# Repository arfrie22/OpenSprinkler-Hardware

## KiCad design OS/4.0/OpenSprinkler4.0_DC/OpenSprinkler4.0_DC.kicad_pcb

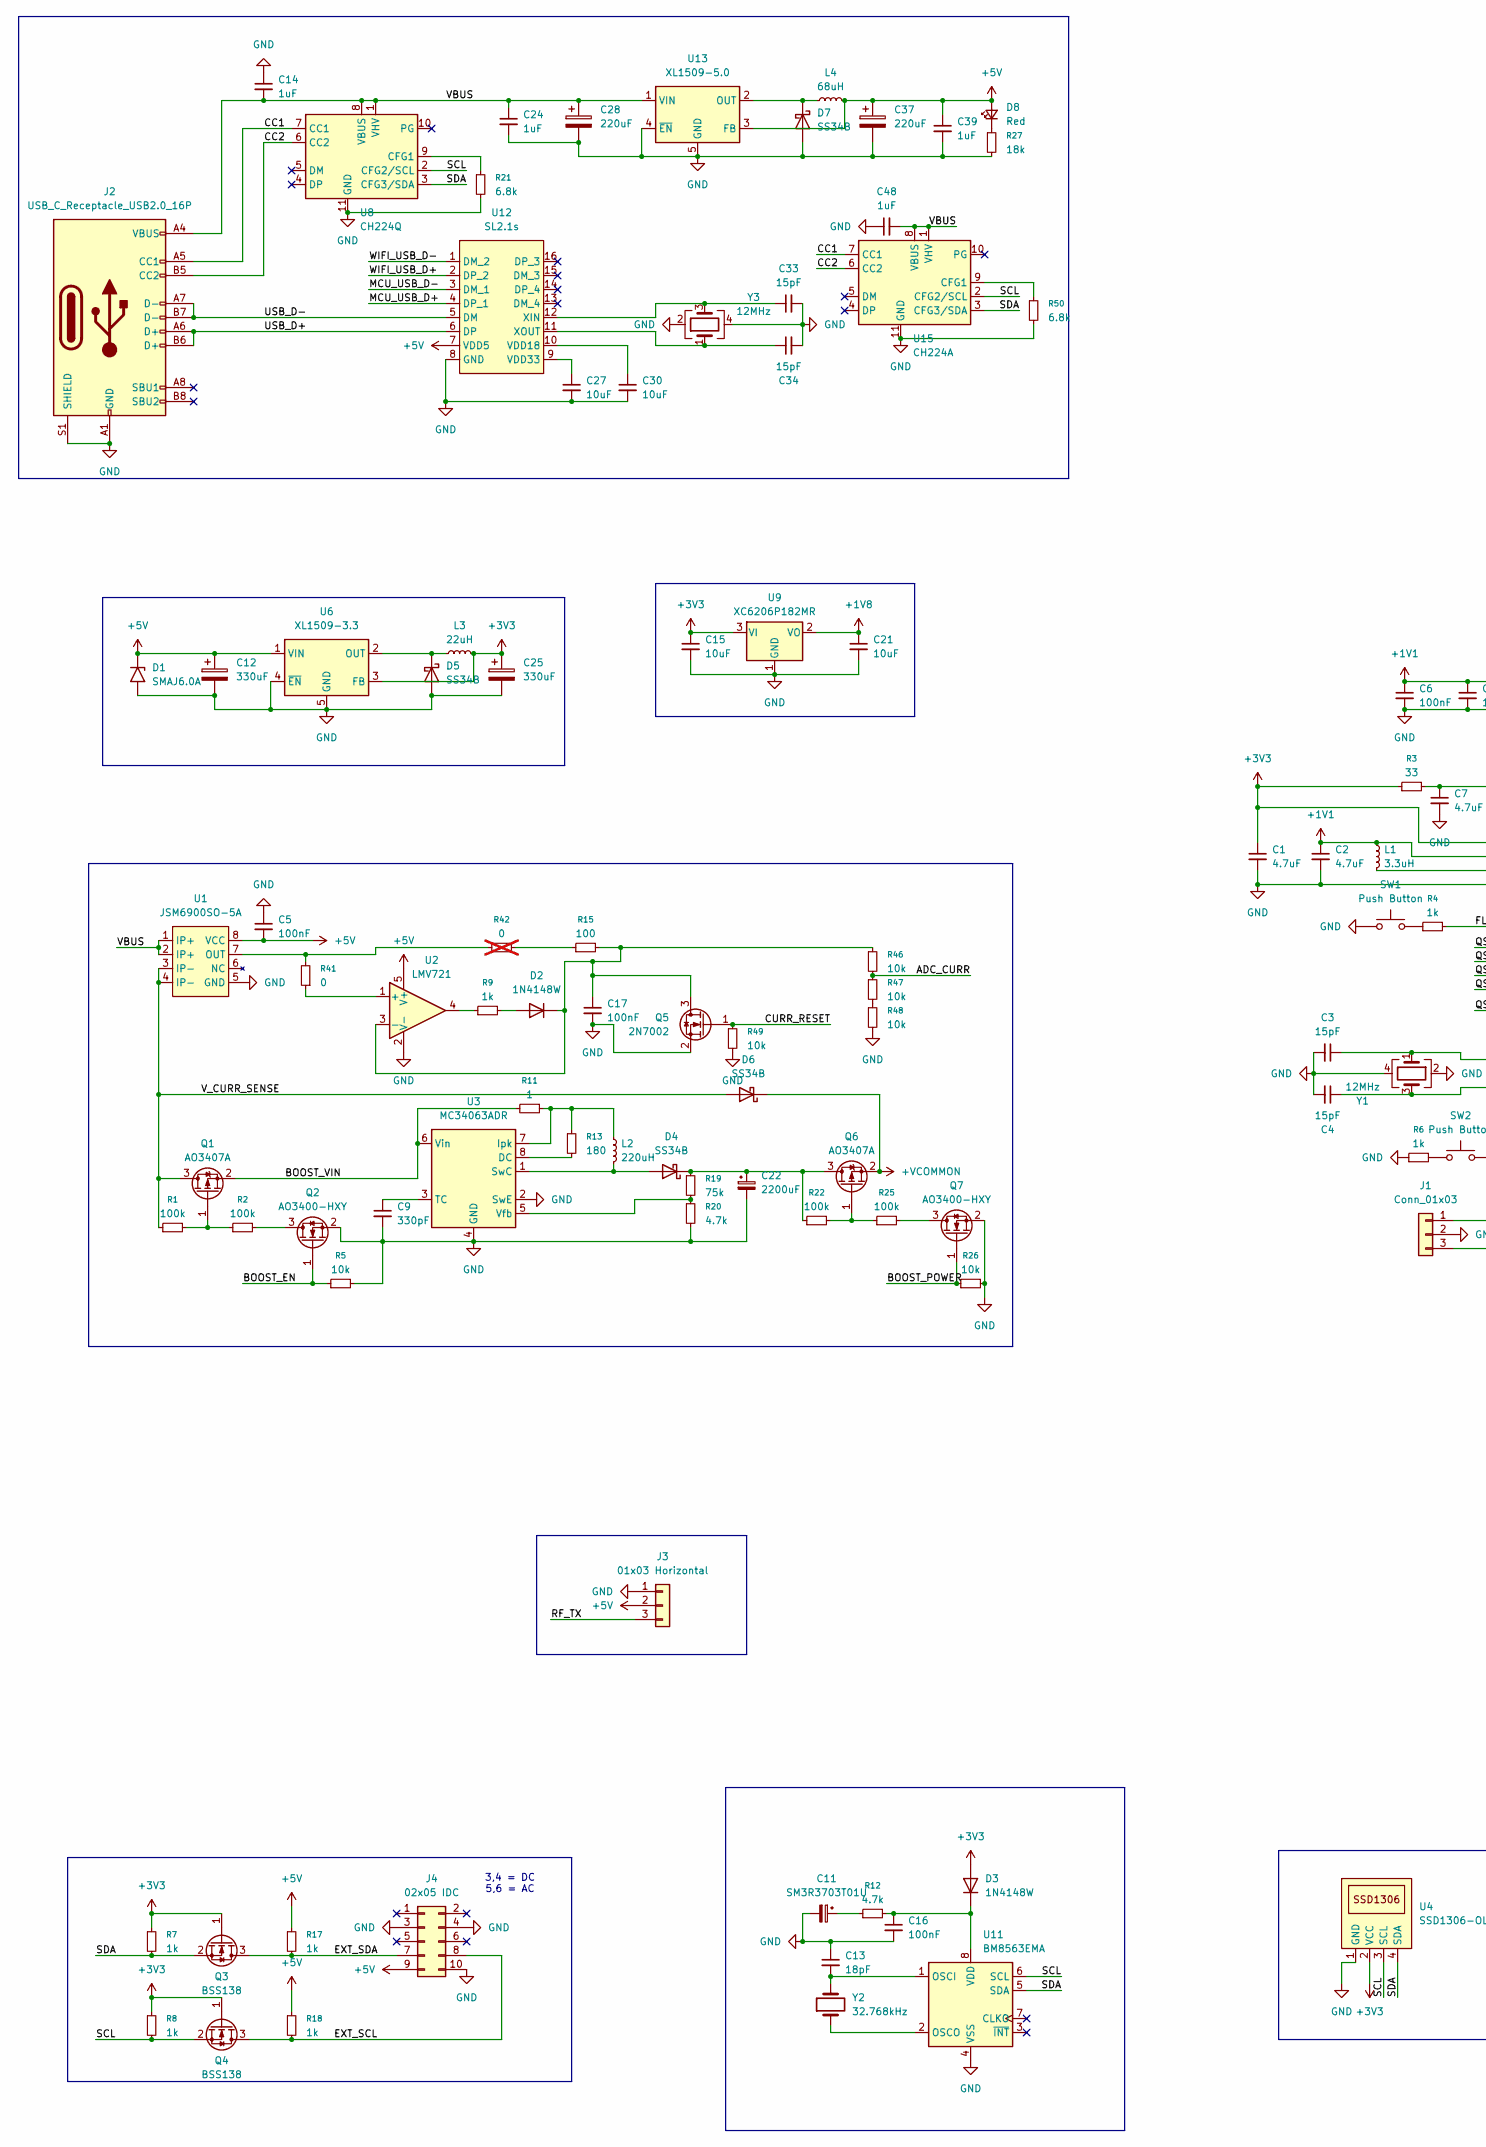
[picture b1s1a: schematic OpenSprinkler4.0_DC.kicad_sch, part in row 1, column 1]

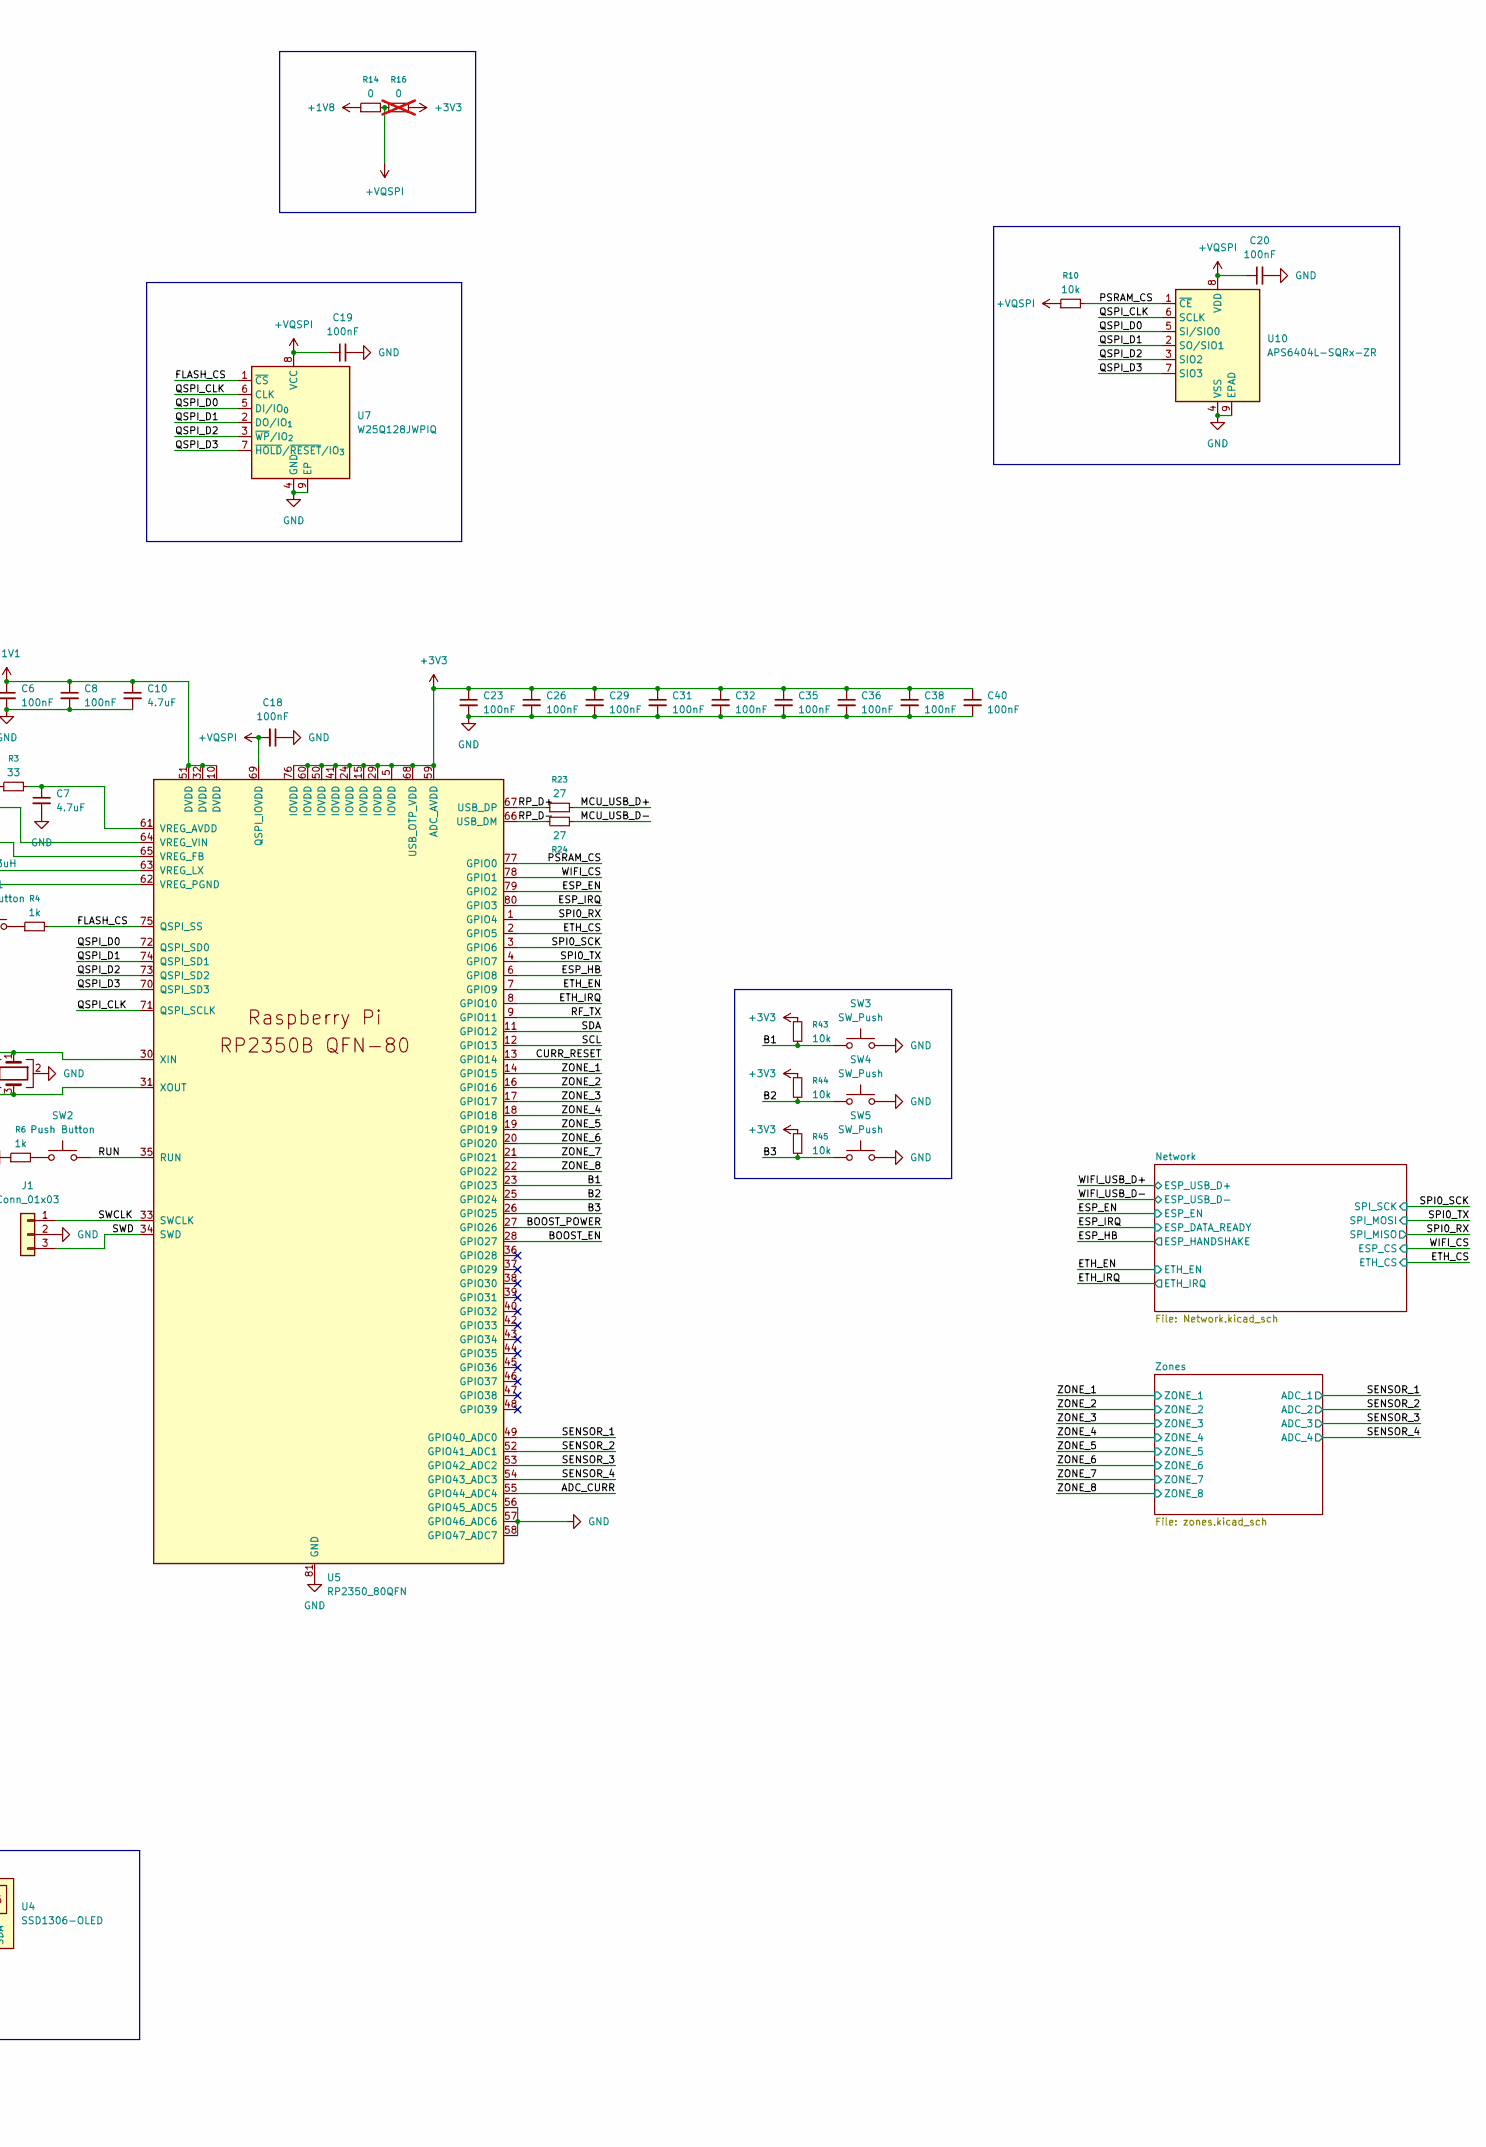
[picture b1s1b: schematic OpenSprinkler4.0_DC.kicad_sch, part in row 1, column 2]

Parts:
C1, C2, C7, C10: 4.7uF; C_0402_1005Metric; LCSC C23733
C3, C4, C33, C34: 15pF; C_0402_1005Metric; LCSC C1548
C5, C6, C8, C16, C17, C18, C19, C20, C23, C26, C29, C31, C32, C35, C36, C38, C40: 100nF; C_0402_1005Metric; LCSC C307331
C9: 330pF; C_0402_1005Metric; LCSC C13533
C11: SM3R3703T01U; SM3R3703T01
C12, C25: 330uF; CP_Radial_D8.0mm_P3.50mm; LCSC C43839
C13: 18pF; C_0402_1005Metric; LCSC C1549
C14, C24, C39, C48: 1uF; C_0603_1608Metric; LCSC C15849
C15, C21, C27, C30: 10uF; C_0603_1608Metric; LCSC C19702
C22: 2200uF; CP_Radial_L20.0mm_D13.0mm_P5.00mm_Horizontal; LCSC C44598
C28, C37: 220uF; CP_Radial_D6.3mm_P2.50mm; LCSC C12450
D1: SMAJ6.0A; D_SMA; LCSC C19077525
D2, D3: 1N4148W; D_SOD-123; LCSC C7420318
D4, D5, D6, D7: SS34B; D_SMB; LCSC C7420366
D8: Red; LED_0603_1608Metric; LCSC C2286
J1: Conn_01x03; JST_XH_B3B-XH-A_1x03_P2.50mm_Vertical; LCSC C144394
J2: USB_C_Receptacle_USB2.0_16P; USB_C_Receptacle_HRO_TYPE-C-31-M-12; LCSC C2927038
J3: 01x03 Horizontal; PinSocket_1x03_P2.54mm_Horizontal; LCSC C2935993
J4: 02x05 IDC; IDC-Header_2x05_P2.54mm_Horizontal; LCSC C9140
L1: 3.3uH; L_Murata_DFE201610P; LCSC C42411119
L2: 220uH; L_Changjiang_FNR8040S; LCSC C168148
L3: 22uH; L_Changjiang_FNR6045S; LCSC C168080
L4: 68uH; L_Changjiang_FNR6045S; LCSC C168091
Q1, Q6: AO3407A; SOT-23; LCSC C3033400
Q2, Q7: AO3400-HXY; SOT-23; LCSC C4748804
Q3, Q4: BSS138; SOT-23; LCSC C7420339
Q5: 2N7002; SOT-23; LCSC C8545
R1, R2, R22, R25: 100k; R_0402_1005Metric; LCSC C25741
R3: 33; R_0402_1005Metric; LCSC C25105
R4, R6, R7, R8, R9, R17, R18: 1k; R_0402_1005Metric; LCSC C11702
R5, R10, R26, R43, R44, R45, R46, R47, R48, R49: 10k; R_0402_1005Metric; LCSC C25744
R11: 1; R_0603_1608Metric; LCSC C22936
R12, R20: 4.7k; R_0402_1005Metric; LCSC C25900
R13: 180; R_0603_1608Metric; LCSC C22828
R14, R41: 0; R_0402_1005Metric; LCSC C17168
R15: 100; R_0402_1005Metric; LCSC C25076
R16, R42: 0; R_0402_1005Metric; LCSC C17168; not fitted
R19: 75k; R_0402_1005Metric; LCSC C25798
R21, R50: 6.8k; R_0402_1005Metric; LCSC C25917
R23, R24: 27; R_0402_1005Metric; LCSC C25100
R27: 18k; R_0402_1005Metric; LCSC C25762
SW1, SW2: Push Button; SW_SPST_SKQG_WithoutStem; LCSC C318884
SW3, SW4, SW5: SW_Push; SW_Tactile_SPST_Angled_PTS645Vx83-2LFS; LCSC C493019
U1: JSM6900SO-5A; SSOP-8_3.9x5.05mm_P1.27mm; LCSC C7496525
U2: LMV721; SOT-23-5; LCSC C20613263
U3: MC34063ADR; SOP-8_3.76x4.96mm_P1.27mm; LCSC C3014308
U4: SSD1306-OLED; JMD0.96D-1
U5: RP2350_80QFN; QFN-80-1EP_10x10mm_P0.4mm_EP3.4x3.4mm; LCSC C42415655
U6: XL1509-3.3; SOIC-8_3.9x4.9mm_P1.27mm; LCSC C2681226
U7: W25Q128JWPIQ; WSON-8-1EP_6x5mm_P1.27mm_EP3.4x4.3mm; LCSC C2689660
U8: CH224Q; Texas_DLH0010A_WSON-10-1EP_2.2x2mm_P0.4mm_EP0.9x1.5mm; LCSC C46061833
U9: XC6206P182MR; SOT-23-3; LCSC C347373
U10: APS6404L-SQRx-ZR; Winbond_USON-8-1EP_3x2mm_P0.5mm_EP0.2x1.6mm; LCSC C43758152
U11: BM8563EMA; SOIC-8_3.9x4.9mm_P1.27mm; LCSC C269878
U12: SL2.1s; SL2.1S; LCSC C2684433
U13: XL1509-5.0; SOIC-8_3.9x4.9mm_P1.27mm; LCSC C2902368
U15: CH224A; SSOP-10-1EP_3.9x4.9mm_P1mm_EP2.1x3.3mm; LCSC C42459160
Y1, Y3: 12MHz; Crystal_SMD_2520-4Pin_2.5x2.0mm; LCSC C7294610
Y2: 32.768kHz; Crystal_SMD_3215-2Pin_3.2x1.5mm; LCSC C32346

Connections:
+1V1: C2.1, C6.1, C8.1, C10.1, L1.1, U5.10 (DVDD), U5.32 (DVDD), U5.51 (DVDD), U5.65 (VREG_FB)
+1V8: C21.1, R14.1, U9.2 (VO)
+3V3: C1.1, C15.1, C23.1, C25.1, C26.1, C29.1, C31.1, C32.1, C35.1, C36.1, C38.1, C40.1, D3.2 (A), L3.2, Q3.1 (G), Q4.1 (G), R3.1, R7.1, R8.1, R16.2, R43.1, R44.1, R45.1, U4.2 (VCC), U5.5 (IOVDD), U5.15 (IOVDD), U5.24 (IOVDD), U5.29 (IOVDD), U5.41 (IOVDD), U5.50 (IOVDD), U5.59 (ADC_AVDD), U5.60 (IOVDD), U5.64 (VREG_VIN), U5.68 (USB_OTP_VDD), U5.76 (IOVDD), U6.3 (FB), U9.3 (VI); also elsewhere on the board
+5V: C5.2, C12.1, C37.1, C39.1, D1.1 (A1), D8.2 (A), J3.2, J4.9, L4.2, R17.1, R18.1, U1.8 (VCC), U2.5 (V+), U6.1 (VIN), U12.7 (VDD5), U13.3 (FB); also elsewhere on the board
+VQSPI: C18.2, C19.1, C20.1, R10.1, R14.2, R16.1, U5.69 (QSPI_IOVDD), U7.8 (VCC), U10.8 (VDD)
/ADC_CURR: R46.2, R47.1, U5.55 (GPIO44_ADC4)
/B1: R43.2, SW3.1, U5.23 (GPIO23)
/B2: R44.2, SW4.1, U5.25 (GPIO24)
/B3: R45.2, SW5.1, U5.26 (GPIO25)
/BOOST_EN: Q2.1 (G), R5.1, U5.28 (GPIO27)
/BOOST_POWER: Q7.1 (G), R26.1, U5.27 (GPIO26)
/BOOST_VIN: Q1.2 (S), R11.2, U3.6 (Vin)
/CC1: J2.A5 (CC1), U8.7 (CC1), U15.7 (CC1)
/CC2: J2.B5 (CC2), U8.6 (CC2), U15.6 (CC2)
/CURR_RESET: Q5.1 (G), R49.1, U5.13 (GPIO14)
/ESP_EN: U5.79 (GPIO2); also elsewhere on the board
/ESP_HB: U5.6 (GPIO8); also elsewhere on the board
/ESP_IRQ: U5.80 (GPIO3); also elsewhere on the board
/ETH_CS: U5.2 (GPIO5); also elsewhere on the board
/ETH_EN: U5.7 (GPIO9); also elsewhere on the board
/ETH_IRQ: U5.8 (GPIO10); also elsewhere on the board
/EXT_SCL: J4.8, Q4.3 (D), R18.2
/EXT_SDA: J4.7, Q3.3 (D), R17.2
/FLASH_CS: R4.2, U5.75 (QSPI_SS), U7.1 (~CS)
/MCU_USB_D+: R23.2, U12.4 (DP_1)
/MCU_USB_D-: R24.2, U12.3 (DM_1)
/PSRAM_CS: R10.2, U5.77 (GPIO0), U10.1 (~CE)
/QSPI_CLK: U5.71 (QSPI_SCLK), U7.6 (CLK), U10.6 (SCLK)
/QSPI_D0: U5.72 (QSPI_SD0), U7.5 (DI/IO_{0}), U10.5 (SI/SIO0)
/QSPI_D1: U5.74 (QSPI_SD1), U7.2 (DO/IO_{1}), U10.2 (SO/SIO1)
/QSPI_D2: U5.73 (QSPI_SD2), U7.3 (~WP/IO_{2}), U10.3 (SIO2)
/QSPI_D3: U5.70 (QSPI_SD3), U7.7 (~HOLD/~RESET/IO_{3}), U10.7 (SIO3)
/RF_TX: J3.3, U5.9 (GPIO11)
/RP_D+: R23.1, U5.67 (USB_DP)
/RP_D-: R24.1, U5.66 (USB_DM)
/RUN: SW2.2, U5.35 (RUN)
/SCL: Q4.2 (S), R8.2, U4.3 (SCL), U5.12 (GPIO13), U8.2 (CFG2/SCL), U11.6 (SCL), U15.2 (CFG2/SCL)
/SDA: Q3.2 (S), R7.2, U4.4 (SDA), U5.11 (GPIO12), U8.3 (CFG3/SDA), U11.5 (SDA), U15.3 (CFG3/SDA)
/SENSOR_1: U5.49 (GPIO40_ADC0); also elsewhere on the board
/SENSOR_2: U5.52 (GPIO41_ADC1); also elsewhere on the board
/SENSOR_3: U5.53 (GPIO42_ADC2); also elsewhere on the board
/SENSOR_4: U5.54 (GPIO43_ADC3); also elsewhere on the board
/SPI0_RX: U5.1 (GPIO4); also elsewhere on the board
/SPI0_SCK: U5.3 (GPIO6); also elsewhere on the board
/SPI0_TX: U5.4 (GPIO7); also elsewhere on the board
/SWCLK: J1.1, U5.33 (SWCLK)
/SWD: J1.3, U5.34 (SWD)
/USB_D+: J2.A6 (D+), J2.B6 (D+), U12.6 (DP)
/USB_D-: J2.A7 (D-), J2.B7 (D-), U12.5 (DM)
/VBUS: C14.2, C24.1, C28.1, C48.2, J2.A4 (VBUS), J2.A9 (VBUS), J2.B4 (VBUS), J2.B9 (VBUS), U1.1 (IP+), U1.2 (IP+), U8.1 (VHV), U8.8 (VBUS), U13.1 (VIN), U15.1 (VHV), U15.8 (VBUS)
/V_CURR_SENSE: D6.2 (A), Q1.3 (D), R1.1, U1.3 (IP-), U1.4 (IP-)
/WIFI_CS: U5.78 (GPIO1); also elsewhere on the board
/WIFI_USB_D+: U12.2 (DP_2); also elsewhere on the board
/WIFI_USB_D-: U12.1 (DM_2); also elsewhere on the board
/ZONE_1: U5.14 (GPIO15); also elsewhere on the board
/ZONE_2: U5.16 (GPIO16); also elsewhere on the board
/ZONE_3: U5.17 (GPIO17); also elsewhere on the board
/ZONE_4: U5.18 (GPIO18); also elsewhere on the board
/ZONE_5: U5.19 (GPIO19); also elsewhere on the board
/ZONE_6: U5.20 (GPIO20); also elsewhere on the board
/ZONE_7: U5.21 (GPIO21); also elsewhere on the board
/ZONE_8: U5.22 (GPIO22); also elsewhere on the board
unnamed: C11.1, R12.1
unnamed: D2.2 (A), R9.2
unnamed: C17.1, D2.1 (K), Q5.3 (D), R15.2, R46.1, U2.3 (-)
unnamed: C16.1, D3.1 (K), R12.2, U11.8 (VDD)
unnamed: D4.2 (A), L2.2, U3.1 (SwC)
unnamed: C22.1, D4.1 (K), Q6.3 (D), R19.1, R22.1
unnamed: D5.1 (K), L3.1, U6.2 (OUT)
unnamed: D7.1 (K), L4.1, U13.2 (OUT)
unnamed: D8.1 (K), R27.1
unnamed: Q1.1 (G), R1.2, R2.1
unnamed: Q2.3 (D), R2.2
unnamed: Q6.1 (G), R22.2, R25.1
unnamed: Q7.3 (D), R25.2
unnamed: R4.1, SW1.2
unnamed: R6.2, SW2.1
unnamed: R9.1, U2.4
unnamed: R15.1, R42.2
unnamed: R47.2, R48.1
unnamed: R41.2, R42.1, U1.7 (OUT)
unnamed: R41.1, U2.1 (+)
unnamed: R13.2, U3.8 (DC)
unnamed: L2.1, R11.1, R13.1, U3.7 (Ipk)
unnamed: C9.1, U3.3 (TC)
unnamed: R19.2, R20.1, U3.5 (Vfb)
unnamed: C7.1, R3.2, U5.61 (VREG_AVDD)
unnamed: L1.2, U5.63 (VREG_LX)
unnamed: C3.1, U5.30 (XIN), Y1.1
unnamed: C4.1, U5.31 (XOUT), Y1.3
unnamed: R21.1, U8.9 (CFG1)
unnamed: C13.2, U11.1 (OSCI), Y2.2
unnamed: U11.2 (OSCO), Y2.1
unnamed: C30.1, U12.10 (VDD18)
unnamed: C27.1, U12.9 (VDD33)
unnamed: C33.1, U12.12 (XIN), Y3.3
unnamed: C34.1, U12.11 (XOUT), Y3.1
unnamed: R50.1, U15.9 (CFG1)

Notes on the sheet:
3,4 = DC 5,6 = AC

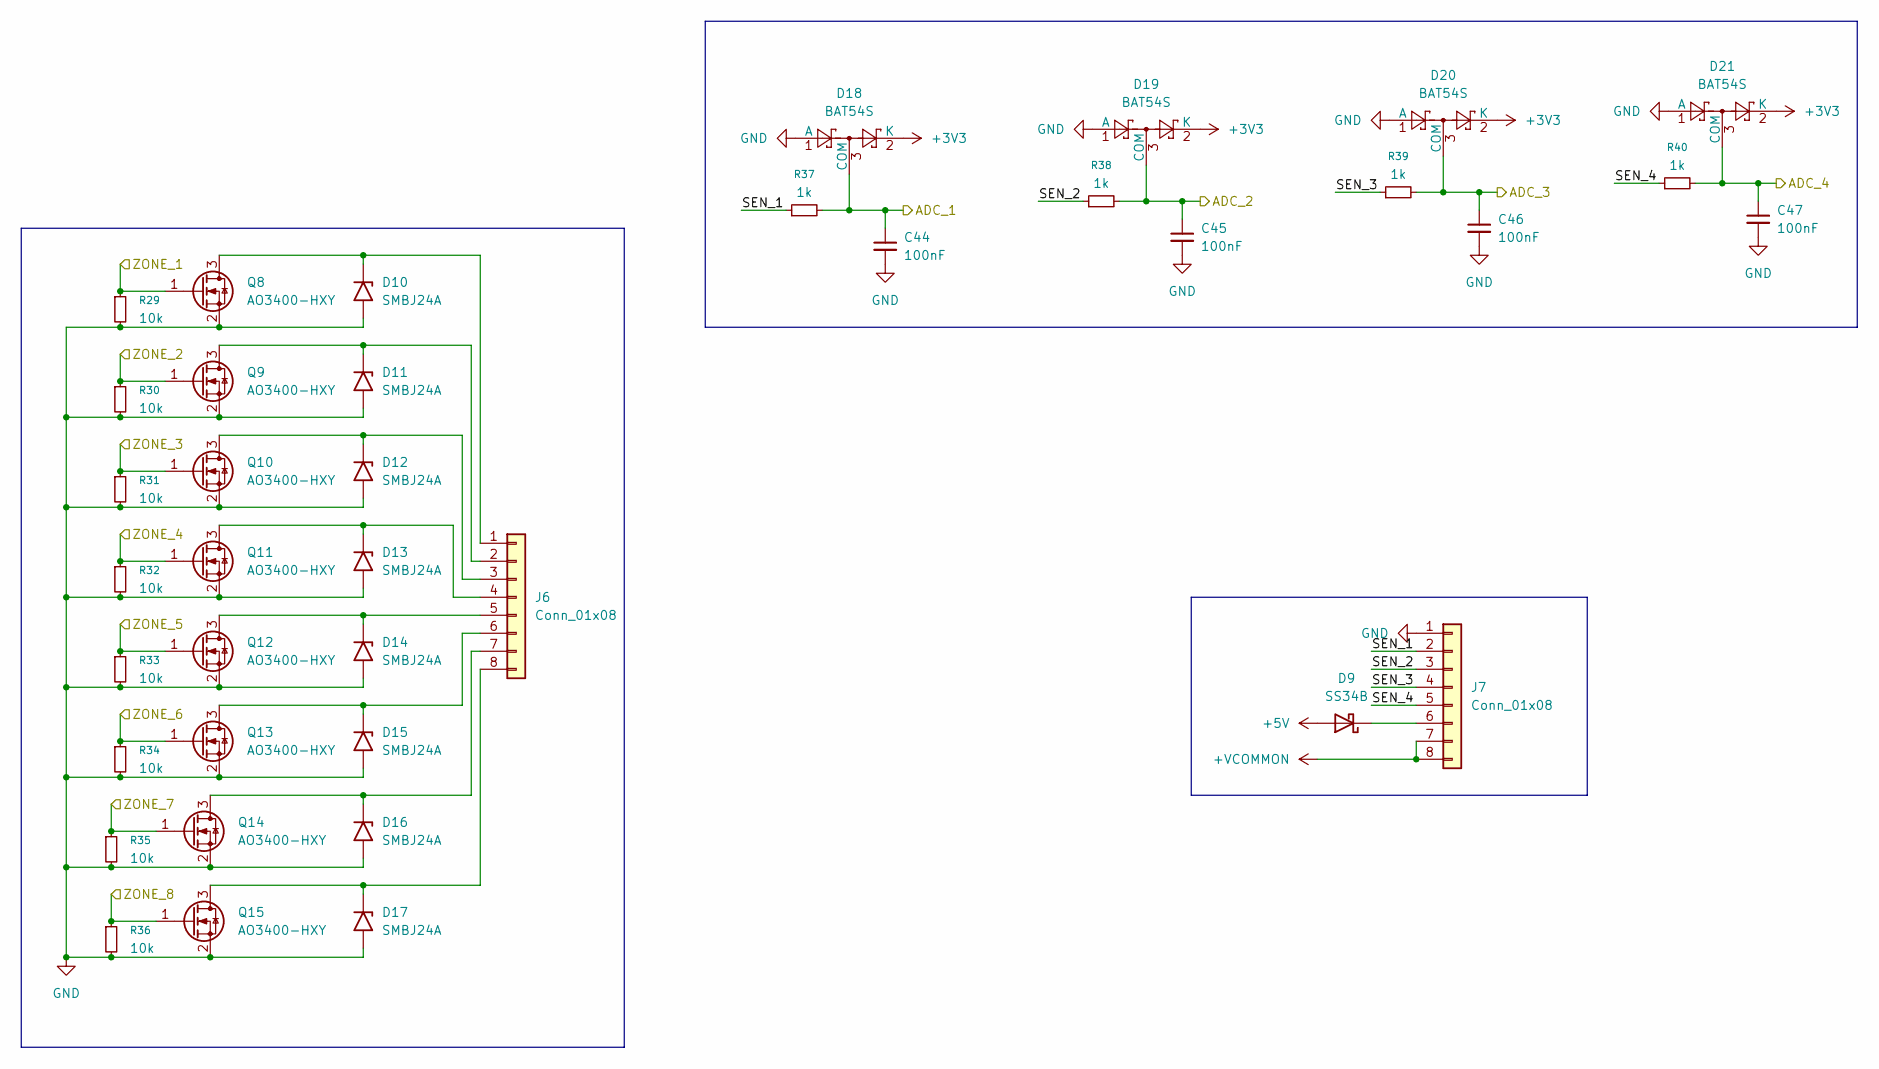
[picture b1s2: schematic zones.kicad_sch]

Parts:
C44, C45, C46, C47: 100nF; C_0402_1005Metric; LCSC C307331
D9: SS34B; D_SMB; LCSC C7420366
D10, D11, D12, D13, D14, D15, D16, D17: SMBJ24A; D_SMB; LCSC C19077578
D18, D19, D20, D21: BAT54S; SOT-23; LCSC C7420333
J6, J7: Conn_01x08; Samtec_HPM-08-05-x-S_Straight_1x08_Pitch5.08mm; LCSC C31423
Q8, Q9, Q10, Q11, Q12, Q13, Q14, Q15: AO3400-HXY; SOT-23; LCSC C4748804
R29, R30, R31, R32, R33, R34, R35, R36: 10k; R_0402_1005Metric; LCSC C25744
R37, R38, R39, R40: 1k; R_0402_1005Metric; LCSC C11702

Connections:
+3V3: D18.2 (K), D19.2 (K), D20.2 (K), D21.2 (K); also elsewhere on the board
+5V: D9.2 (A); also elsewhere on the board
/SENSOR_1: C44.1, D18.3 (COM), R37.2; also elsewhere on the board
/SENSOR_2: C45.1, D19.3 (COM), R38.2; also elsewhere on the board
/SENSOR_3: C46.1, D20.3 (COM), R39.2; also elsewhere on the board
/SENSOR_4: C47.1, D21.3 (COM), R40.2; also elsewhere on the board
/ZONE_1: Q8.1 (G), R29.1; also elsewhere on the board
/ZONE_2: Q9.1 (G), R30.1; also elsewhere on the board
/ZONE_3: Q10.1 (G), R31.1; also elsewhere on the board
/ZONE_4: Q11.1 (G), R32.1; also elsewhere on the board
/ZONE_5: Q12.1 (G), R33.1; also elsewhere on the board
/ZONE_6: Q13.1 (G), R34.1; also elsewhere on the board
/ZONE_7: Q14.1 (G), R35.1; also elsewhere on the board
/ZONE_8: Q15.1 (G), R36.1; also elsewhere on the board
/Zones/SEN_1: J7.2, R37.1
/Zones/SEN_2: J7.3, R38.1
/Zones/SEN_3: J7.4, R39.1
/Zones/SEN_4: J7.5, R40.1
unnamed: D9.1 (K), J7.6
unnamed: D10.1 (A1), J6.1, Q8.3 (D)
unnamed: D11.1 (A1), J6.2, Q9.3 (D)
unnamed: D12.1 (A1), J6.3, Q10.3 (D)
unnamed: D13.1 (A1), J6.4, Q11.3 (D)
unnamed: D14.1 (A1), J6.5, Q12.3 (D)
unnamed: D15.1 (A1), J6.6, Q13.3 (D)
unnamed: D16.1 (A1), J6.7, Q14.3 (D)
unnamed: D17.1 (A1), J6.8, Q15.3 (D)

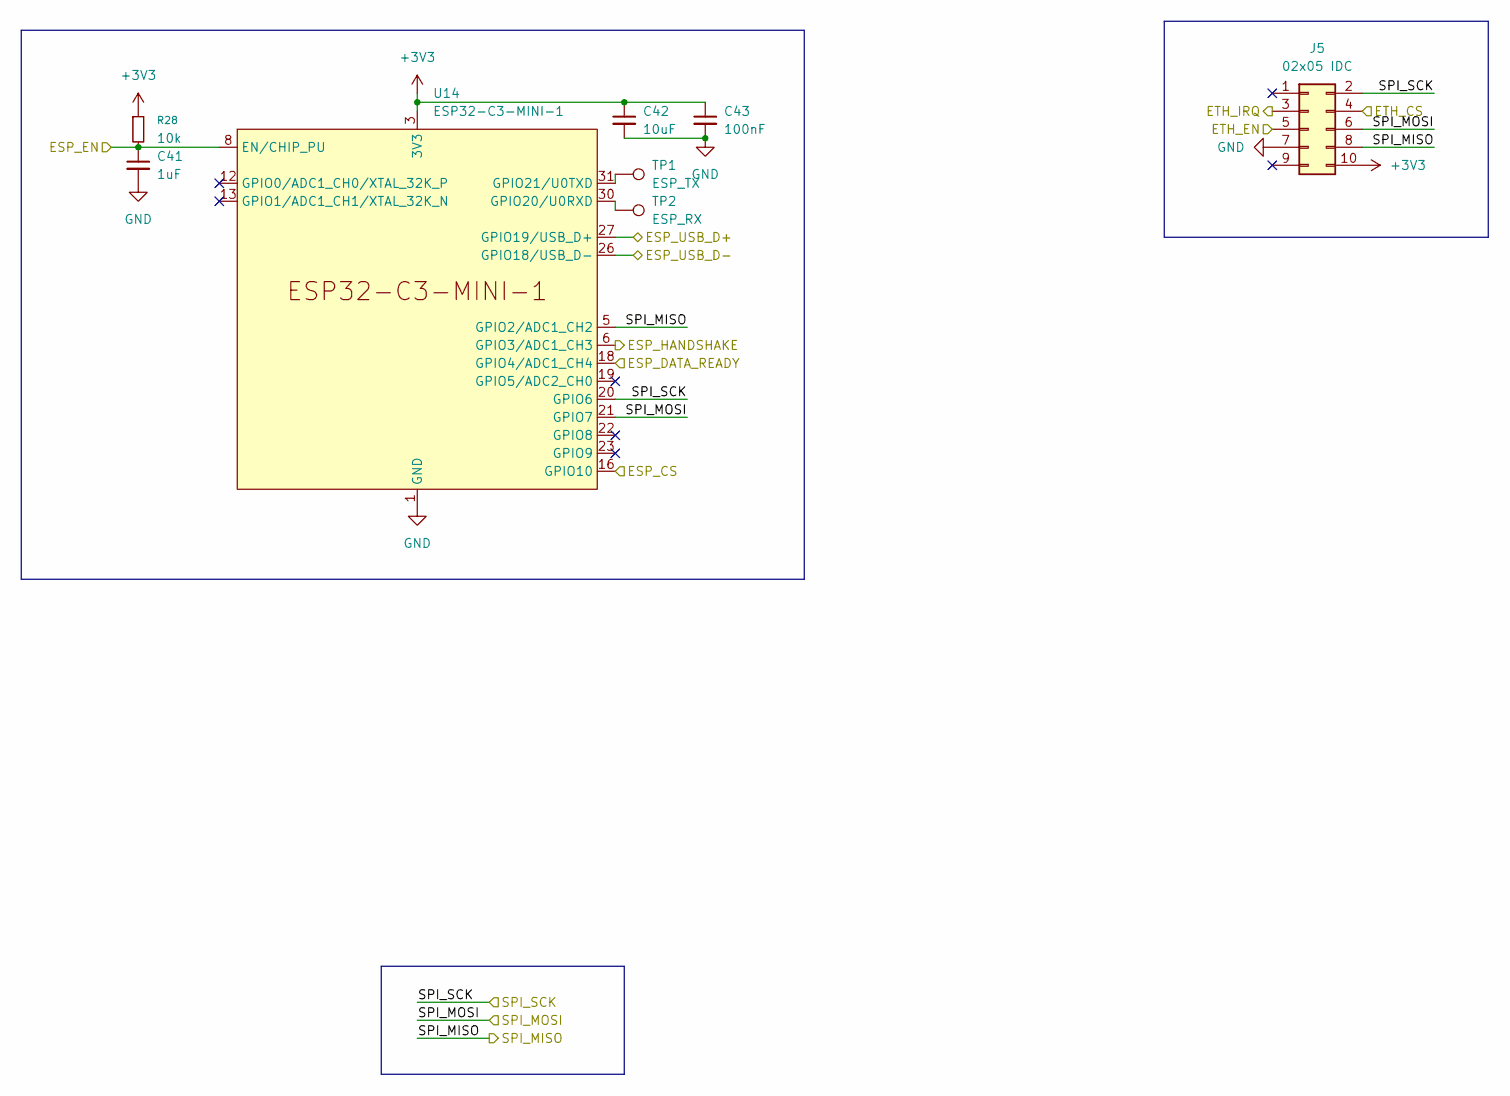
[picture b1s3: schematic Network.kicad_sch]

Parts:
C41: 1uF; C_0603_1608Metric; LCSC C15849
C42: 10uF; C_0603_1608Metric; LCSC C19702
C43: 100nF; C_0402_1005Metric; LCSC C307331
J5: 02x05 IDC; IDC-Header_2x05_P2.54mm_Horizontal; LCSC C9140
R28: 10k; R_0402_1005Metric; LCSC C25744
TP1: ESP_TX; TestPoint_Pad_D1.5mm
TP2: ESP_RX; TestPoint_Pad_D1.5mm
U14: ESP32-C3-MINI-1; LCSC C41349510

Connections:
+3V3: C42.1, C43.1, J5.10, R28.1, U14.3 (3V3); also elsewhere on the board
/ESP_EN: C41.1, R28.2, U14.8 (EN/CHIP_PU); also elsewhere on the board
/ESP_HB: U14.6 (GPIO3/ADC1_CH3); also elsewhere on the board
/ESP_IRQ: U14.18 (GPIO4/ADC1_CH4); also elsewhere on the board
/ETH_CS: J5.4; also elsewhere on the board
/ETH_EN: J5.5; also elsewhere on the board
/ETH_IRQ: J5.3; also elsewhere on the board
/SPI0_RX: J5.8, U14.5 (GPIO2/ADC1_CH2); also elsewhere on the board
/SPI0_SCK: J5.2, U14.20 (GPIO6); also elsewhere on the board
/SPI0_TX: J5.6, U14.21 (GPIO7); also elsewhere on the board
/WIFI_CS: U14.16 (GPIO10); also elsewhere on the board
/WIFI_USB_D+: U14.27 (GPIO19/USB_D+); also elsewhere on the board
/WIFI_USB_D-: U14.26 (GPIO18/USB_D-); also elsewhere on the board
unnamed: TP2.1, U14.30 (GPIO20/U0RXD)
unnamed: TP1.1, U14.31 (GPIO21/U0TXD)

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
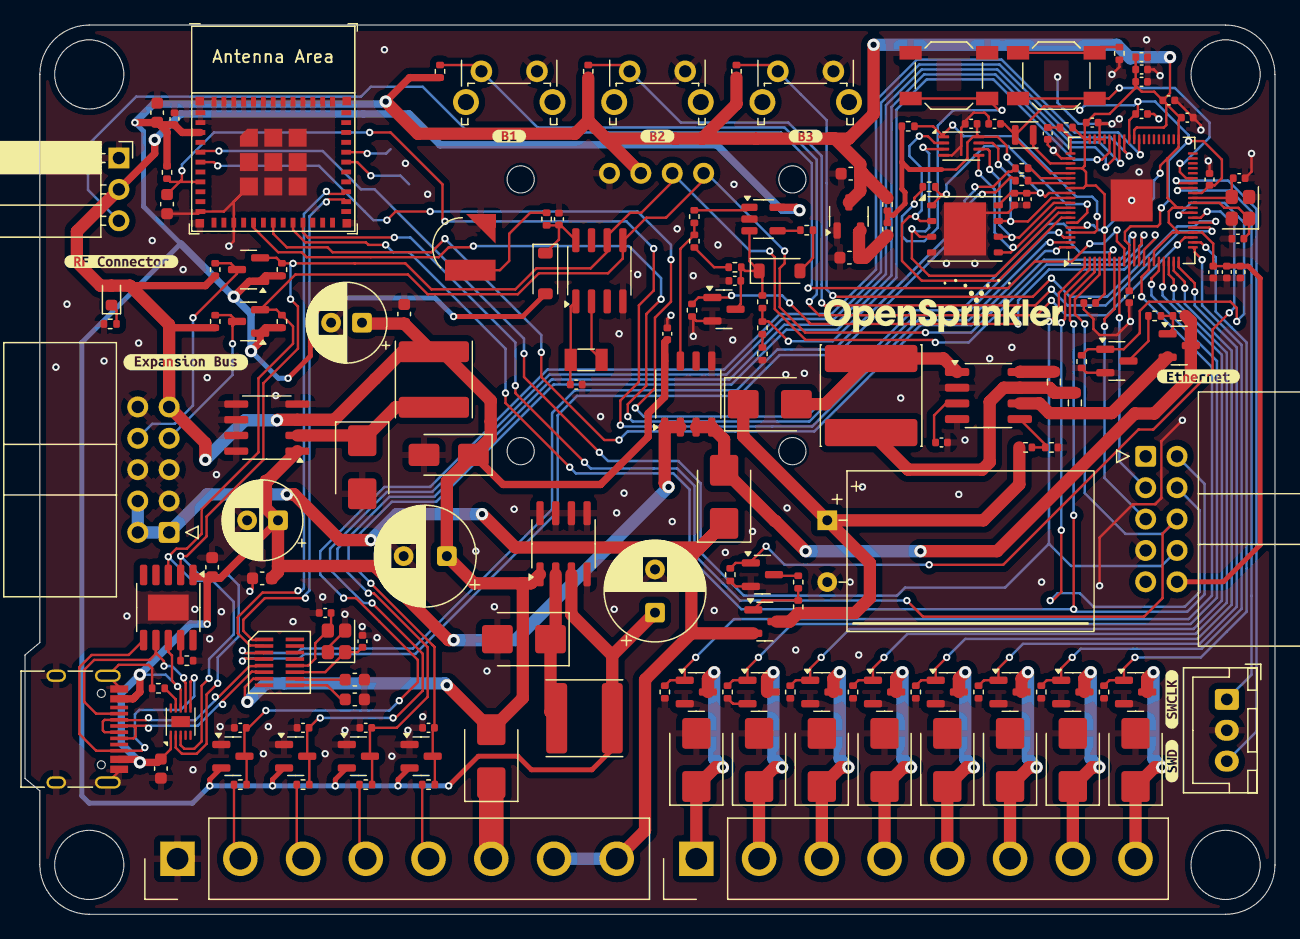
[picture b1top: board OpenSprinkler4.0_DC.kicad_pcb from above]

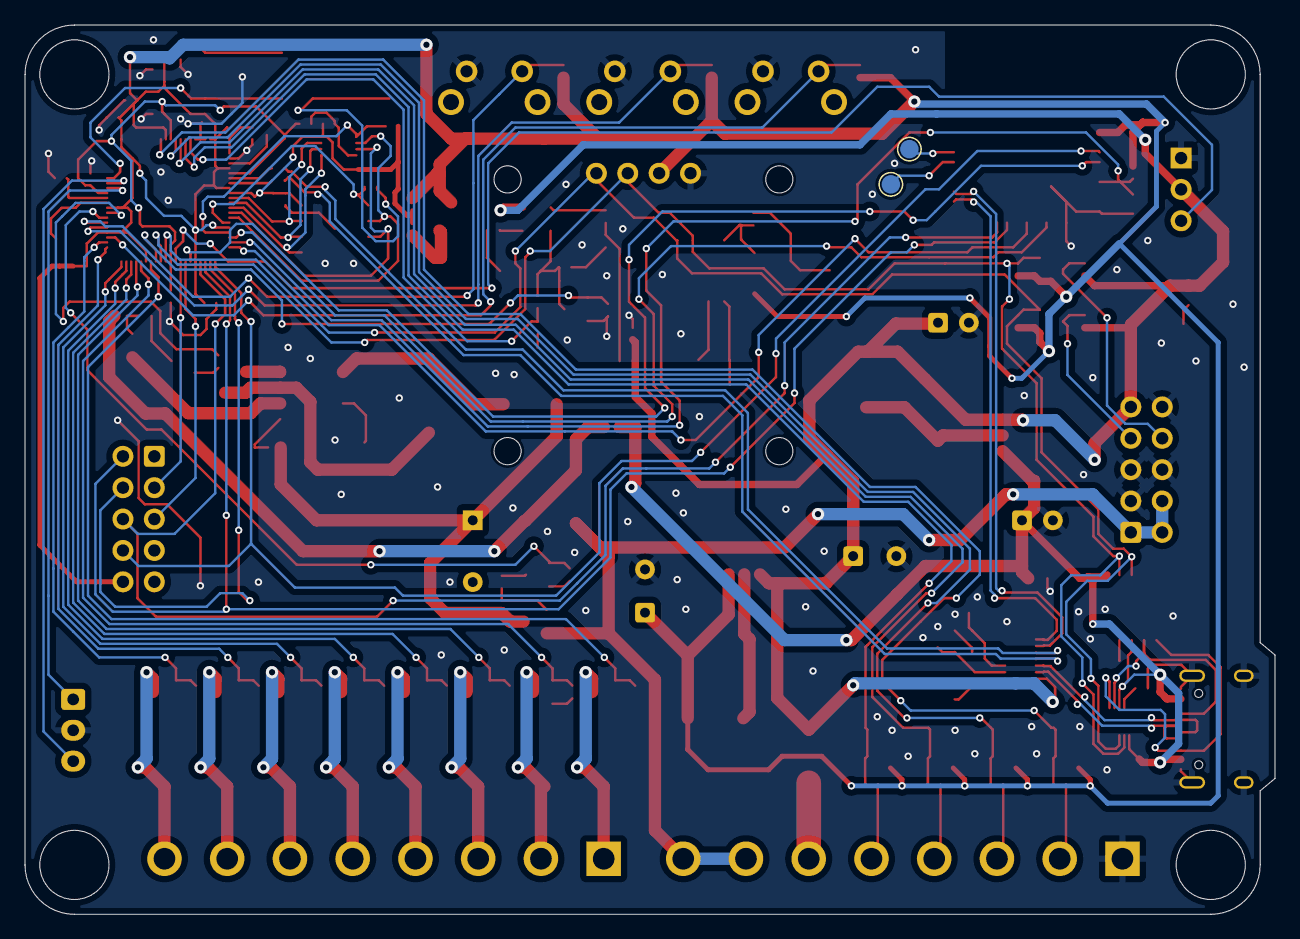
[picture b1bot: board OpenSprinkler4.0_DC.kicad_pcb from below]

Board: 2 copper layers, 101.2 x 72.0 mm, 178 parts (2 on the bottom side), 115 nets.

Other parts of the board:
kibuzzard-688CCB3A: G***; kibuzzard-688CCB3A
kibuzzard-688CCB7A: G***; kibuzzard-688CCB7A
kibuzzard-688CCB16: G***; kibuzzard-688CCB16
kibuzzard-688CCB53: G***; kibuzzard-688CCB53
kibuzzard-688CCBAC: G***; kibuzzard-688CCBAC
kibuzzard-688CCBBF: G***; kibuzzard-688CCBBF
kibuzzard-688CCBE1: G***; kibuzzard-688CCBE1
kibuzzard-688CCBE6: G***; kibuzzard-688CCBE6
